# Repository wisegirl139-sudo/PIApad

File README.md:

<h2 align="center">PIApad</h2>
hiya, so piapad is short for piano pad, now its not really a piano or a pad, its actually a mini keyboard on a card shaped pcb. So sue me for misleading or wtv but it is a catchier name , i bet kevin hart would agree.

anyways now piapad has 8 keys made from exposed copper pads that use acd type sensoring.(horrible wording but yes).Now peronally the scmatic is peak and so is the pcb but the firmware is a bit mid but hey always room for improvement.
+this will also soon have its compatibe website.

how it works is each "key" acts a keyboard key (like genuinely abcd etc on your keyboard) then these key values are used on the website to make sounds.(eg x tricggers f#). and thats pretty much a whole summary of it

why - i wanted to learn more about circuit boards and try out more stuff (ive only ever made a hack pad this is my second project). and also do successful pcb art (forgot to remove solder mask from the copper art on the old ones:'(
anywyas
<h2 align="center">PCB</h2>

<h2 align="center">schmatic </h2>

<h2 align="center">Render</h2>

<h2 align="center">BOM</h2>

| number | item name | link | price |
| ------------- | ------------- | ------------- | ------------- |
| 6 | 100 nF capacitor, 0603	0603 100nF 50V X7R SMD capacitor  |https://shorturl.at/AdGyc| ￡4.19 |
| 4  | 10 µF capacitor, 0603	0603 10uF 10V X5R SMD capacitor  |https://shorturl.at/QeLva| ￡1.02 |
| 2 | Yellow LED, 0603	0603 yellow LED 1608 SMD 2V 20mA | https://shorturl.at/DPzo3| ￡1.24 |
| 1 | 1×4, 2.54 mm vertical header	1x4 2.54mm male pin header straight |  https://shorturl.at/FfzzU | £0.74|
| 2 | 30 Ω, 0603	0603 30R 30 ohm SMD resistor 1% | https://rb.gy/cfu7y2 | ￡1.28 |
| 2	| 5.1 kΩ, 0603	0603 5.1K 5100 ohm SMD resistor 1% | https://rb.gy/cfu7y2 | ￡1.28 |
| 1	| 10 kΩ, 0603	0603 10K SMD resistor 1% | https://rb.gy/cfu7y2 | ￡1.28 |
| 2 |	1 kΩ, 0603	0603 1K SMD resistor 1% | https://rb.gy/cfu7y2 | ￡1.28 |
| 1 |	STM32L442KCU6	STM32L442KCU6 QFN32|https://shorturl.at/c5ISe | ￡4.23 |
| 1 |	MIC5504-3.3YM5	MIC5504-3.3YM5 SOT23-5 3.3V| https://www.aliexpress.com/item/1005009487683111.html|￡4.42 |

<h2 align="center">total price= £19.66</h2>

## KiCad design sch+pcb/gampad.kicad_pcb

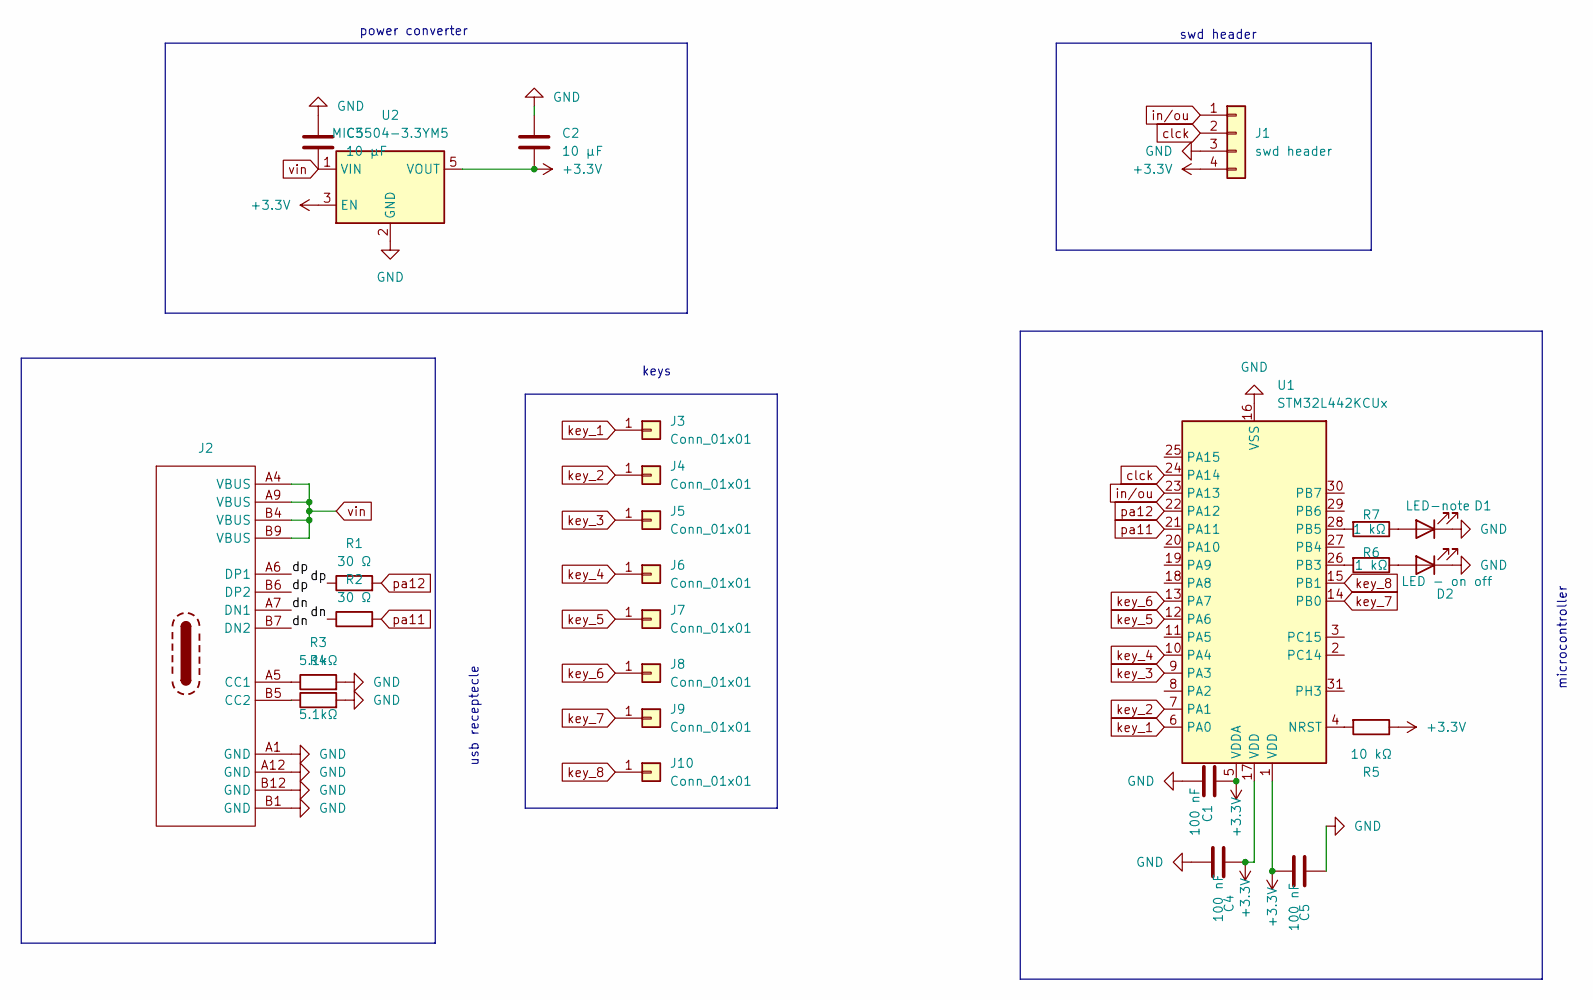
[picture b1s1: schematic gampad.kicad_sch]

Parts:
C1, C4, C5: 100 nF; C_0603_1608Metric
C2, C3: 10 µF; C_0603_1608Metric
D1: LED-note; LED_0603_1608Metric
D2: LED - on off; LED_0603_1608Metric
J1: swd header; PinHeader_1x04_P2.54mm_Vertical
J2: USB_C_Receptacle_HRO_TYPE-C-31-M-12
J3: Conn_01x01; key1
J4: Conn_01x01; key2
J5, J7, J9: Conn_01x01; key3
J6, J8: Conn_01x01; key4
J10: Conn_01x01; key5
R1, R2: 30 Ω; R_0603_1608Metric
R3, R4: 5.1kΩ; R_0603_1608Metric
R5: 10 kΩ; R_0603_1608Metric
R6, R7: 1 kΩ; R_0603_1608Metric
U1: STM32L442KCUx; QFN-32-1EP_5x5mm_P0.5mm_EP3.45x3.45mm
U2: MIC5504-3.3YM5; SOT-23-5

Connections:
+3.3V: C1.1, C2.1, C4.1, C5.2, J1.4, R5.1, U1.1 (VDD), U1.5 (VDDA), U1.17 (VDD), U2.3 (EN), U2.5 (VOUT)
/dn: J2.A7 (DN1), J2.B7 (DN2), R2.1
/dp: J2.A6 (DP1), J2.B6 (DP2), R1.1
GND: C1.2, C2.2, C3.2, C4.2, C5.1, D1.1 (K), D2.1 (K), J1.3, J2.A1 (GND), J2.A12 (GND), J2.B1 (GND), J2.B12 (GND), R3.2, R4.2, U1.16 (VSS), U1.32 (VSS), U1.33 (VSS), U2.2 (GND)
unnamed: D1.2 (A), R7.1
unnamed: D2.2 (A), R6.1
unnamed: J2.A5 (CC1), R3.1
unnamed: J2.B5 (CC2), R4.1
unnamed: R5.2, U1.4 (NRST)
unnamed: R6.2, U1.26 (PB3)
unnamed: R7.2, U1.28 (PB5)
clck: J1.2, U1.24 (PA14)
in/ou: J1.1, U1.23 (PA13)
key_1: J3.1 (Pin_1_1), U1.6 (PA0)
key_2: J4.1 (Pin_1_1), U1.7 (PA1)
key_3: J5.1 (Pin_1_1), U1.9 (PA3)
key_4: J6.1 (Pin_1_1), U1.10 (PA4)
key_5: J7.1 (Pin_1_1), U1.12 (PA6)
key_6: J8.1 (Pin_1_1), U1.13 (PA7)
key_7: J9.1 (Pin_1_1), U1.14 (PB0)
key_8: J10.1 (Pin_1_1), U1.15 (PB1)
pa11: R2.2, U1.21 (PA11)
pa12: R1.2, U1.22 (PA12)
vin: C3.1, J2.A4 (VBUS), J2.A9 (VBUS), J2.B4 (VBUS), J2.B9 (VBUS), U2.1 (VIN)

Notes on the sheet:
keys
swd header
power converter
usb receptecle
microcontroller

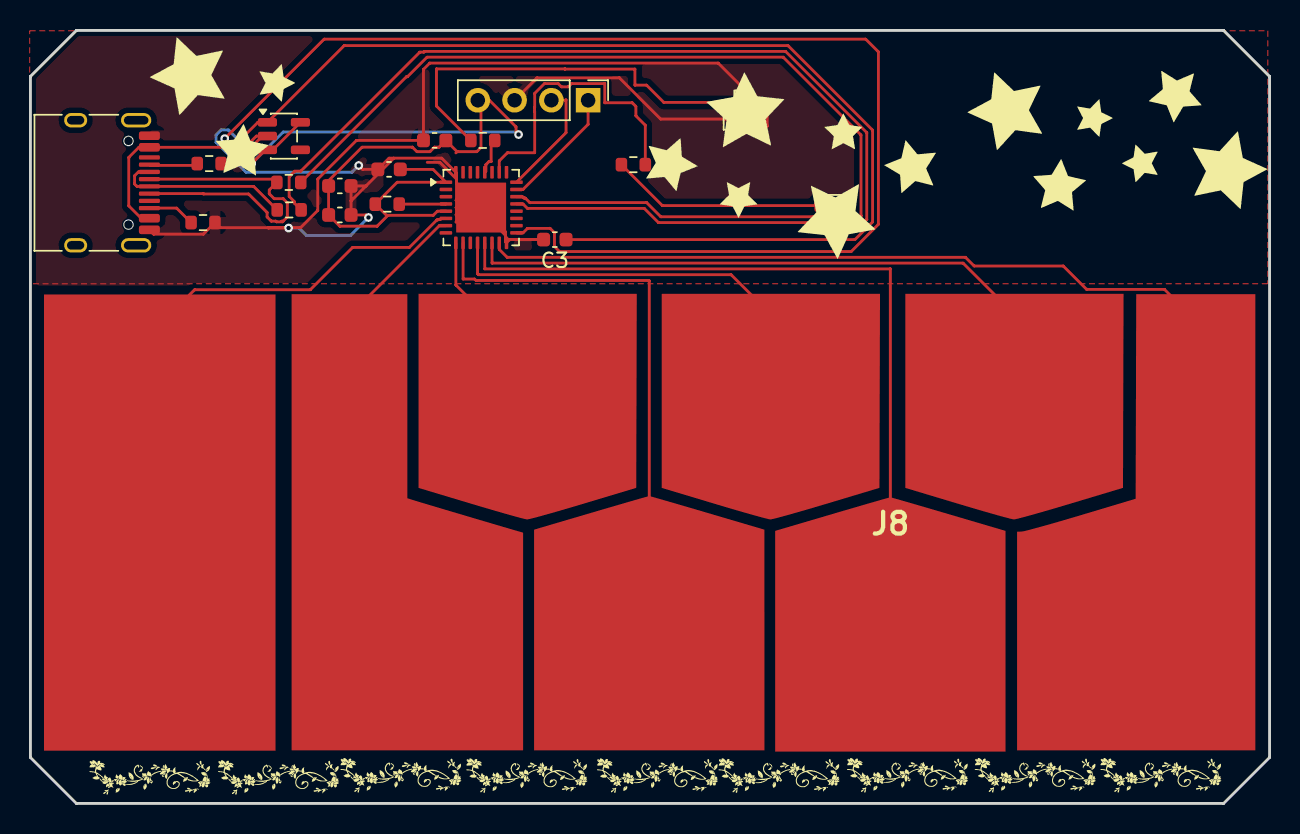
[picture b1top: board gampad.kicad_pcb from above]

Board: 2 copper layers, 85.6 x 53.4 mm, 26 parts (0 on the bottom side), 24 nets.

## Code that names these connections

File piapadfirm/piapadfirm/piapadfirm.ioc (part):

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Mcu.Name=STM32L442KCUx
Mcu.Package=UFQFPN32
Mcu.UserName=STM32L442KCUx
PA0.Signal=ADCx_IN5
PA1.Signal=ADCx_IN6
PA11.Mode=Device
PA11.Signal=USB_DM
PA12.Mode=Device
PA12.Signal=USB_DP
PA3.Signal=ADCx_IN8
PA4.Signal=ADCx_IN9
PA6.Signal=ADCx_IN11
PA7.Signal=ADCx_IN12
PB0.Signal=ADCx_IN15
PB1.Signal=ADCx_IN16
PB3\ (JTDO-TRACESWO).Signal=GPIO_Output
PB5.Signal=GPIO_Output
RCC.HSE_VALUE=8000000
RCC.SYSCLKFreq_VALUE=80000000
RCC.SYSCLKSource=RCC_SYSCLKSOURCE_PLLCLK
board=custom
